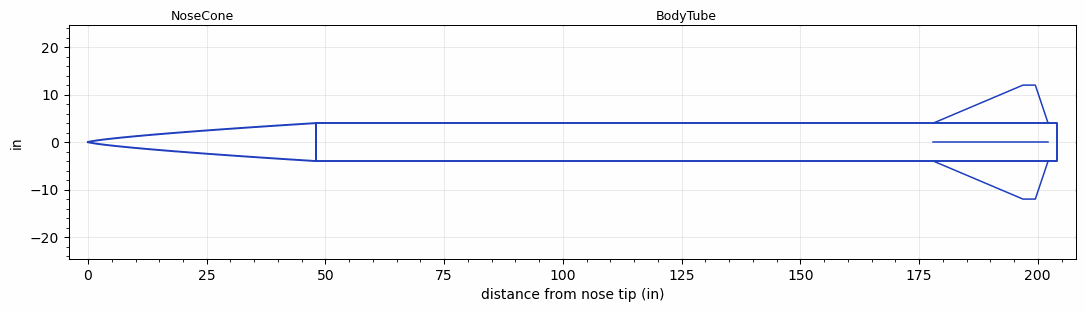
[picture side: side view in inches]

<RASAeroDocument>
 <FileVersion>2</FileVersion>
 <RocketDesign>
  <NoseCone>
   <Length>48</Length>
   <Diameter>8</Diameter>
   <Shape>Power Law</Shape>
   <Location>0</Location>
   <PowerLaw>0.75</PowerLaw>
  </NoseCone>
  <BodyTube>
   <Length>156</Length>
   <Diameter>8</Diameter>
   <LaunchShoeArea>9</LaunchShoeArea>
   <Location>48</Location>
   <Fin>
    <Count>4</Count>
    <Chord>24.17</Chord>
    <Span>8</Span>
    <SweepDistance>18.88</SweepDistance>
    <TipChord>2.6</TipChord>
    <Thickness>0.5</Thickness>
    <Location>26</Location>
    <AirfoilSection>Rounded</AirfoilSection>
   </Fin>
  </BodyTube>
  <Surface>Smooth (Zero Roughness)</Surface>
  <ModifiedBarrowman>False</ModifiedBarrowman>
  <Turbulence>False</Turbulence>
  <UseBooster1>False</UseBooster1>
  <UseBooster2>False</UseBooster2>
 </RocketDesign>
 <LaunchSite>
  <Altitude>0</Altitude>
  <Pressure>0</Pressure>
  <RodAngle>0</RodAngle>
  <RodLength>4</RodLength>
  <Temperature>74</Temperature>
  <WindSpeed>0</WindSpeed>
 </LaunchSite>
 <Recovery>
  <Altitude1>1000</Altitude1>
  <Altitude2>1000</Altitude2>
  <DeviceType1>None</DeviceType1>
  <DeviceType2>None</DeviceType2>
  <Event1>False</Event1>
  <Event2>False</Event2>
  <Size1>1</Size1>
  <Size2>1</Size2>
  <EventType1>None</EventType1>
  <EventType2>None</EventType2>
  <CD1>1.33</CD1>
  <CD2>1.33</CD2>
 </Recovery>
 <SimulationList>
  <Simulation>
   <SustainerEngine>Q19134  (TRC)</SustainerEngine>
   <SustainerLaunchWt>330</SustainerLaunchWt>
   <SustainerNozzleDiameter>6.75</SustainerNozzleDiameter>
   <SustainerCG>100</SustainerCG>
   <SustainerIgnitionDelay>0</SustainerIgnitionDelay>
   <Booster1SeparationDelay>0</Booster1SeparationDelay>
   <Booster1IgnitionDelay>0</Booster1IgnitionDelay>
   <IncludeBooster1>False</IncludeBooster1>
   <Booster2Delay>0</Booster2Delay>
   <IncludeBooster2>False</IncludeBooster2>
   <TimetoApogee>34.54021</TimetoApogee>
   <MaxAltitude>26482.94</MaxAltitude>
   <MaxVelocity>2276.705</MaxVelocity>
   <OptimumWt>330</OptimumWt>
   <OptimumMaxAlt>330</OptimumMaxAlt>
  </Simulation>
  <Simulation>
   <SustainerEngine>Q19134  (TRC)</SustainerEngine>
   <SustainerLaunchWt>250</SustainerLaunchWt>
   <SustainerCG>100</SustainerCG>
   <SustainerIgnitionDelay>0</SustainerIgnitionDelay>
   <Booster1SeparationDelay>0</Booster1SeparationDelay>
   <Booster1IgnitionDelay>0</Booster1IgnitionDelay>
   <IncludeBooster1>False</IncludeBooster1>
   <Booster2Delay>0</Booster2Delay>
   <IncludeBooster2>False</IncludeBooster2>
   <TimetoApogee>29.58058</TimetoApogee>
   <MaxAltitude>24408.26</MaxAltitude>
   <MaxVelocity>2492.985</MaxVelocity>
   <OptimumWt>328.125</OptimumWt>
   <OptimumMaxAlt>328.125</OptimumMaxAlt>
  </Simulation>
  <Simulation>
   <SustainerEngine>Q19134  (TRC)</SustainerEngine>
   <SustainerLaunchWt>300</SustainerLaunchWt>
   <SustainerNozzleDiameter>6.75</SustainerNozzleDiameter>
   <SustainerCG>75</SustainerCG>
   <SustainerIgnitionDelay>0</SustainerIgnitionDelay>
   <Booster1SeparationDelay>0</Booster1SeparationDelay>
   <Booster1IgnitionDelay>0</Booster1IgnitionDelay>
   <IncludeBooster1>False</IncludeBooster1>
   <Booster2Delay>0</Booster2Delay>
   <IncludeBooster2>False</IncludeBooster2>
   <TimetoApogee>33.24043</TimetoApogee>
   <MaxAltitude>26411.05</MaxAltitude>
   <MaxVelocity>2410.502</MaxVelocity>
   <OptimumWt>322.5</OptimumWt>
   <OptimumMaxAlt>322.5</OptimumMaxAlt>
  </Simulation>
  <Simulation>
   <SustainerEngine>Q19134  (TRC)</SustainerEngine>
   <SustainerLaunchWt>275</SustainerLaunchWt>
   <SustainerNozzleDiameter>6.75</SustainerNozzleDiameter>
   <SustainerCG>50</SustainerCG>
   <SustainerIgnitionDelay>0</SustainerIgnitionDelay>
   <Booster1SeparationDelay>0</Booster1SeparationDelay>
   <Booster1IgnitionDelay>0</Booster1IgnitionDelay>
   <IncludeBooster1>False</IncludeBooster1>
   <Booster2Delay>0</Booster2Delay>
   <IncludeBooster2>False</IncludeBooster2>
   <TimetoApogee>31.82063</TimetoApogee>
   <MaxAltitude>26100.56</MaxAltitude>
   <MaxVelocity>2525.93</MaxVelocity>
   <OptimumWt>323.125</OptimumWt>
   <OptimumMaxAlt>323.125</OptimumMaxAlt>
  </Simulation>
 </SimulationList>
</RASAeroDocument>
